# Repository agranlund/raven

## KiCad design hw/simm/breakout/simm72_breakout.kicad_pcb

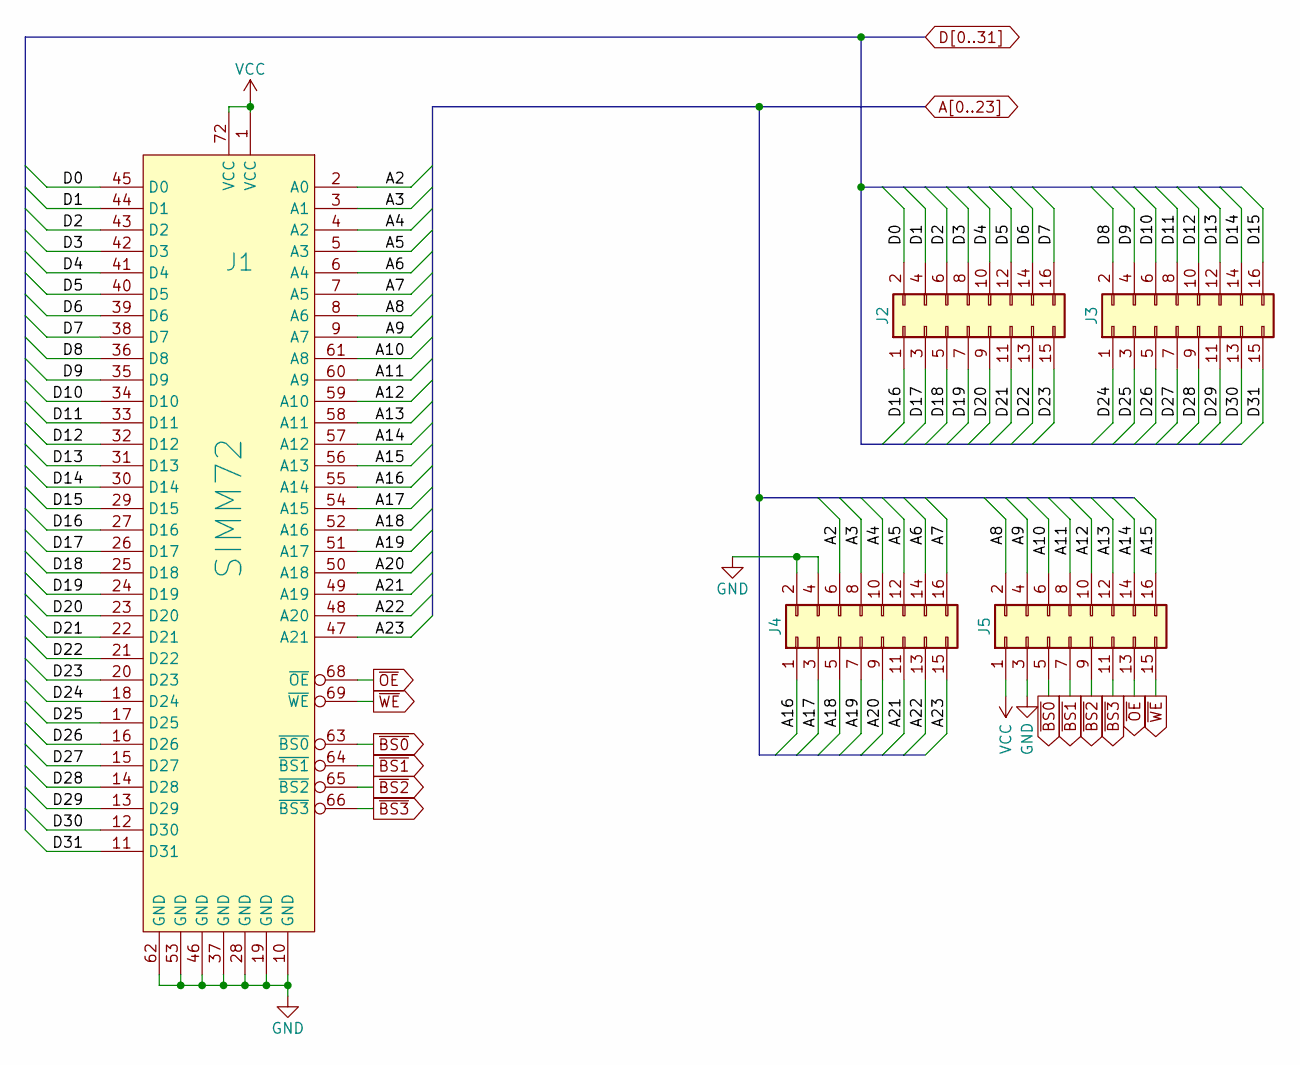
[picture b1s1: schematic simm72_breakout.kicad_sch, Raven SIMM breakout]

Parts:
J1: SIMM72; SIMM72_edge
J2, J3, J4, J5: Conn_02x08_Row_Letter_Last; PinHeader_2x08_P2.54mm_Vertical

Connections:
A2: J1.2 (A0), J4.6
A3: J1.3 (A1), J4.8
A4: J1.4 (A2), J4.10
A5: J1.5 (A3), J4.12
A6: J1.6 (A4), J4.14
A7: J1.7 (A5), J4.16
A8: J1.8 (A6), J5.2
A9: J1.9 (A7), J5.4
A10: J1.61 (A8), J5.6
A11: J1.60 (A9), J5.8
A12: J1.59 (A10), J5.10
A13: J1.58 (A11), J5.12
A14: J1.57 (A12), J5.14
A15: J1.56 (A13), J5.16
A16: J1.55 (A14), J4.1
A17: J1.54 (A15), J4.3
A18: J1.52 (A16), J4.5
A19: J1.51 (A17), J4.7
A20: J1.50 (A18), J4.9
A21: J1.49 (A19), J4.11
A22: J1.48 (A20), J4.13
A23: J1.47 (A21), J4.15
D0: J1.45 (D0), J2.2
D1: J1.44 (D1), J2.4
D2: J1.43 (D2), J2.6
D3: J1.42 (D3), J2.8
D4: J1.41 (D4), J2.10
D5: J1.40 (D5), J2.12
D6: J1.39 (D6), J2.14
D7: J1.38 (D7), J2.16
D8: J1.36 (D8), J3.2
D9: J1.35 (D9), J3.4
D10: J1.34 (D10), J3.6
D11: J1.33 (D11), J3.8
D12: J1.32 (D12), J3.10
D13: J1.31 (D13), J3.12
D14: J1.30 (D14), J3.14
D15: J1.29 (D15), J3.16
D16: J1.27 (D16), J2.1
D17: J1.26 (D17), J2.3
D18: J1.25 (D18), J2.5
D19: J1.24 (D19), J2.7
D20: J1.23 (D20), J2.9
D21: J1.22 (D21), J2.11
D22: J1.21 (D22), J2.13
D23: J1.20 (D23), J2.15
D24: J1.18 (D24), J3.1
D25: J1.17 (D25), J3.3
D26: J1.16 (D26), J3.5
D27: J1.15 (D27), J3.7
D28: J1.14 (D28), J3.9
D29: J1.13 (D29), J3.11
D30: J1.12 (D30), J3.13
D31: J1.11 (D31), J3.15
GND: J1.10 (GND), J1.19 (GND), J1.28 (GND), J1.37 (GND), J1.46 (GND), J1.53 (GND), J1.62 (GND), J4.2, J4.4, J5.3
VCC: J1.1 (VCC), J1.72 (VCC), J5.1
~BS0: J1.63 (~BS0), J5.5
~BS1: J1.64 (~BS1), J5.7
~BS2: J1.65 (~BS2), J5.9
~BS3: J1.66 (~BS3), J5.11
~OE: J1.68 (~OE), J5.13
~WE: J1.69 (~WE), J5.15

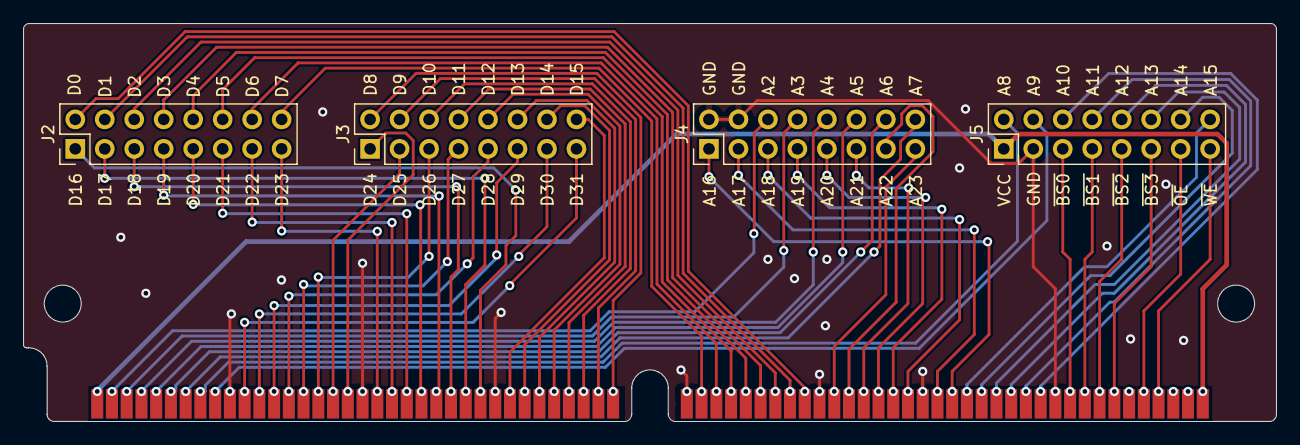
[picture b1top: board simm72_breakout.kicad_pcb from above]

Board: 2 copper layers, 108.0 x 34.3 mm, 5 parts (0 on the bottom side), 62 nets.

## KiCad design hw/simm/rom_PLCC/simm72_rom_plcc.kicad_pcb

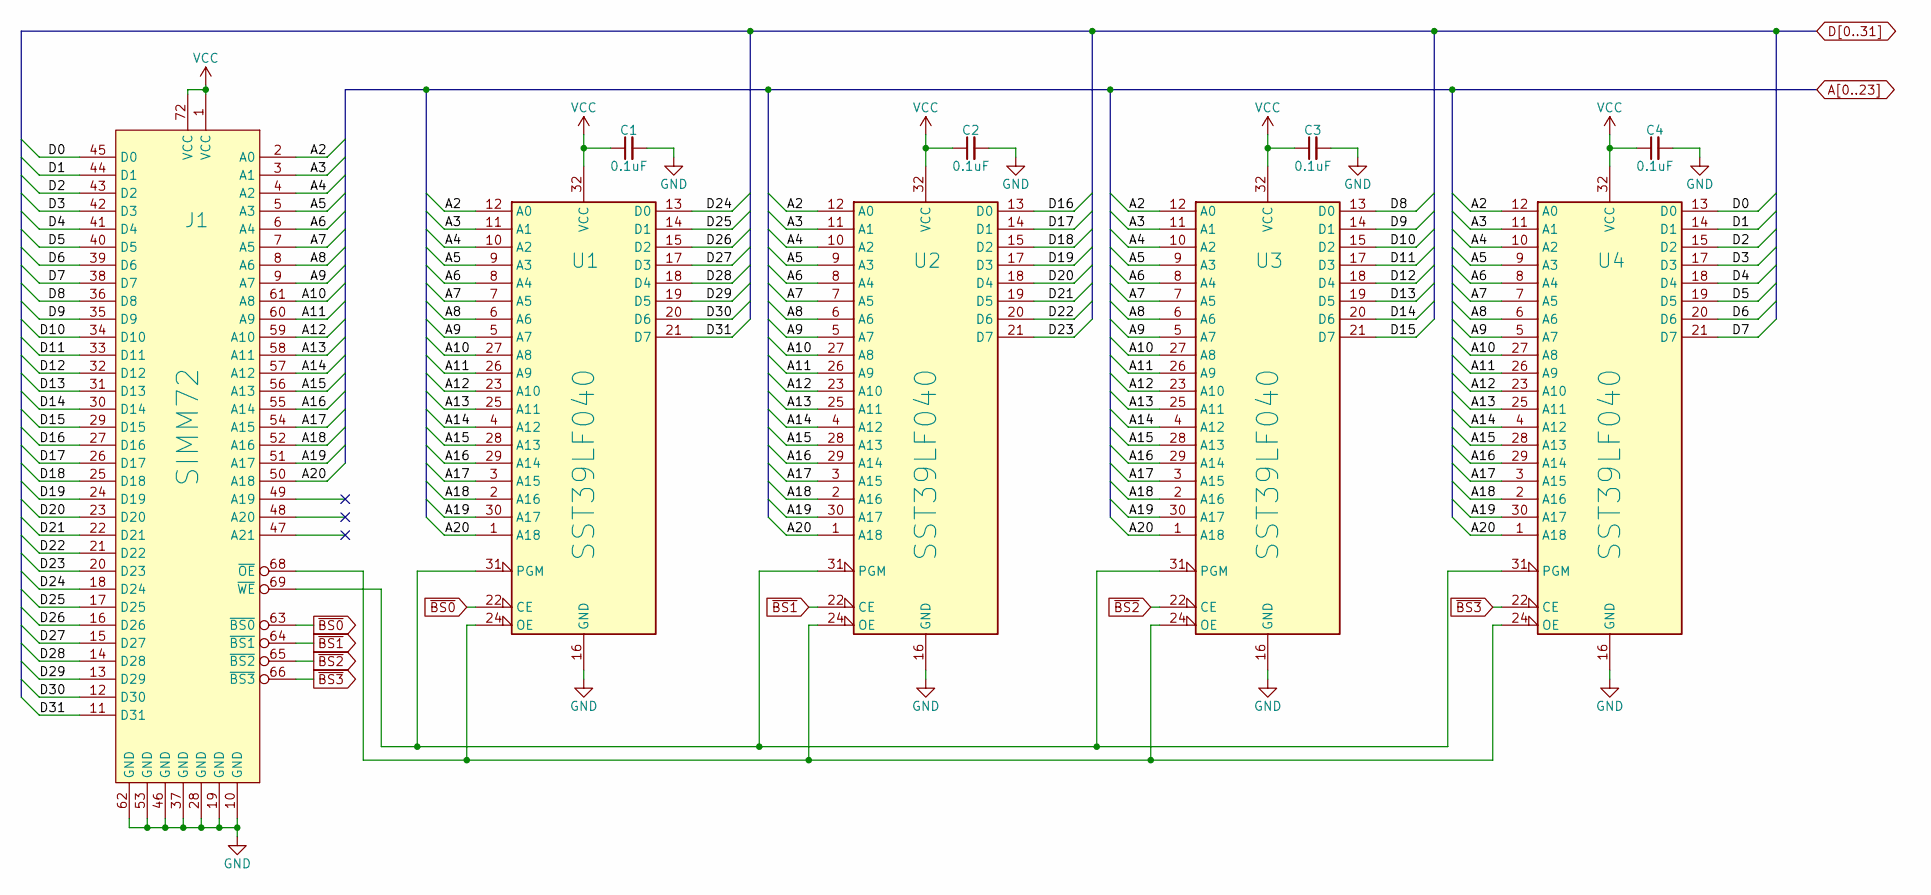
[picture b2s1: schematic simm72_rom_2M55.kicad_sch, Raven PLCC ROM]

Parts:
C1, C2, C3, C4: 0.1uF; C_1206_3216Metric_Pad1.33x1.80mm_HandSolder; Manufacturer_Part_Number C1206C104K5RACTU
J1: SIMM72; SIMM72_edge
U1, U2, U3, U4: SST39LF040; PLCC-32_THT-Socket; Manufacturer_Part_Number SST39LF040-55-4C-NHE-T

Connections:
A2: J1.2 (A0), U1.12 (A0), U2.12 (A0), U3.12 (A0), U4.12 (A0)
A3: J1.3 (A1), U1.11 (A1), U2.11 (A1), U3.11 (A1), U4.11 (A1)
A4: J1.4 (A2), U1.10 (A2), U2.10 (A2), U3.10 (A2), U4.10 (A2)
A5: J1.5 (A3), U1.9 (A3), U2.9 (A3), U3.9 (A3), U4.9 (A3)
A6: J1.6 (A4), U1.8 (A4), U2.8 (A4), U3.8 (A4), U4.8 (A4)
A7: J1.7 (A5), U1.7 (A5), U2.7 (A5), U3.7 (A5), U4.7 (A5)
A8: J1.8 (A6), U1.6 (A6), U2.6 (A6), U3.6 (A6), U4.6 (A6)
A9: J1.9 (A7), U1.5 (A7), U2.5 (A7), U3.5 (A7), U4.5 (A7)
A10: J1.61 (A8), U1.27 (A8), U2.27 (A8), U3.27 (A8), U4.27 (A8)
A11: J1.60 (A9), U1.26 (A9), U2.26 (A9), U3.26 (A9), U4.26 (A9)
A12: J1.59 (A10), U1.23 (A10), U2.23 (A10), U3.23 (A10), U4.23 (A10)
A13: J1.58 (A11), U1.25 (A11), U2.25 (A11), U3.25 (A11), U4.25 (A11)
A14: J1.57 (A12), U1.4 (A12), U2.4 (A12), U3.4 (A12), U4.4 (A12)
A15: J1.56 (A13), U1.28 (A13), U2.28 (A13), U3.28 (A13), U4.28 (A13)
A16: J1.55 (A14), U1.29 (A14), U2.29 (A14), U3.29 (A14), U4.29 (A14)
A17: J1.54 (A15), U1.3 (A15), U2.3 (A15), U3.3 (A15), U4.3 (A15)
A18: J1.52 (A16), U1.2 (A16), U2.2 (A16), U3.2 (A16), U4.2 (A16)
A19: J1.51 (A17), U1.30 (A17), U2.30 (A17), U3.30 (A17), U4.30 (A17)
A20: J1.50 (A18), U1.1 (A18), U2.1 (A18), U3.1 (A18), U4.1 (A18)
D0: J1.45 (D0), U4.13 (D0)
D1: J1.44 (D1), U4.14 (D1)
D2: J1.43 (D2), U4.15 (D2)
D3: J1.42 (D3), U4.17 (D3)
D4: J1.41 (D4), U4.18 (D4)
D5: J1.40 (D5), U4.19 (D5)
D6: J1.39 (D6), U4.20 (D6)
D7: J1.38 (D7), U4.21 (D7)
D8: J1.36 (D8), U3.13 (D0)
D9: J1.35 (D9), U3.14 (D1)
D10: J1.34 (D10), U3.15 (D2)
D11: J1.33 (D11), U3.17 (D3)
D12: J1.32 (D12), U3.18 (D4)
D13: J1.31 (D13), U3.19 (D5)
D14: J1.30 (D14), U3.20 (D6)
D15: J1.29 (D15), U3.21 (D7)
D16: J1.27 (D16), U2.13 (D0)
D17: J1.26 (D17), U2.14 (D1)
D18: J1.25 (D18), U2.15 (D2)
D19: J1.24 (D19), U2.17 (D3)
D20: J1.23 (D20), U2.18 (D4)
D21: J1.22 (D21), U2.19 (D5)
D22: J1.21 (D22), U2.20 (D6)
D23: J1.20 (D23), U2.21 (D7)
D24: J1.18 (D24), U1.13 (D0)
D25: J1.17 (D25), U1.14 (D1)
D26: J1.16 (D26), U1.15 (D2)
D27: J1.15 (D27), U1.17 (D3)
D28: J1.14 (D28), U1.18 (D4)
D29: J1.13 (D29), U1.19 (D5)
D30: J1.12 (D30), U1.20 (D6)
D31: J1.11 (D31), U1.21 (D7)
GND: C1.2, C2.2, C3.2, C4.2, J1.10 (GND), J1.19 (GND), J1.28 (GND), J1.37 (GND), J1.46 (GND), J1.53 (GND), J1.62 (GND), U1.16 (GND), U2.16 (GND), U3.16 (GND), U4.16 (GND)
unnamed: J1.68 (~OE), U1.24 (OE), U2.24 (OE), U3.24 (OE), U4.24 (OE)
unnamed: J1.69 (~WE), U1.31 (PGM), U2.31 (PGM), U3.31 (PGM), U4.31 (PGM)
VCC: C1.1, C2.1, C3.1, C4.1, J1.1 (VCC), J1.72 (VCC), U1.32 (VCC), U2.32 (VCC), U3.32 (VCC), U4.32 (VCC)
~BS0: J1.63 (~BS0), U1.22 (CE)
~BS1: J1.64 (~BS1), U2.22 (CE)
~BS2: J1.65 (~BS2), U3.22 (CE)
~BS3: J1.66 (~BS3), U4.22 (CE)

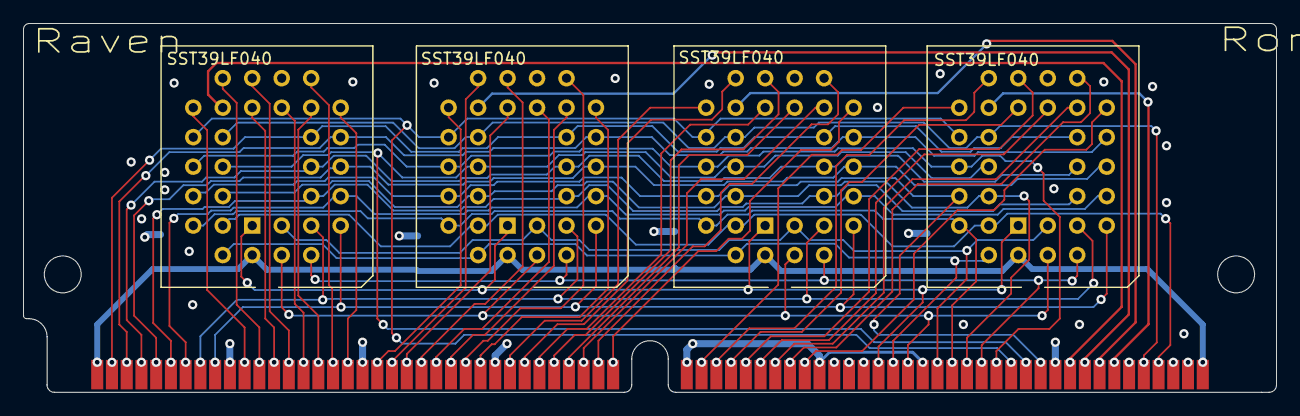
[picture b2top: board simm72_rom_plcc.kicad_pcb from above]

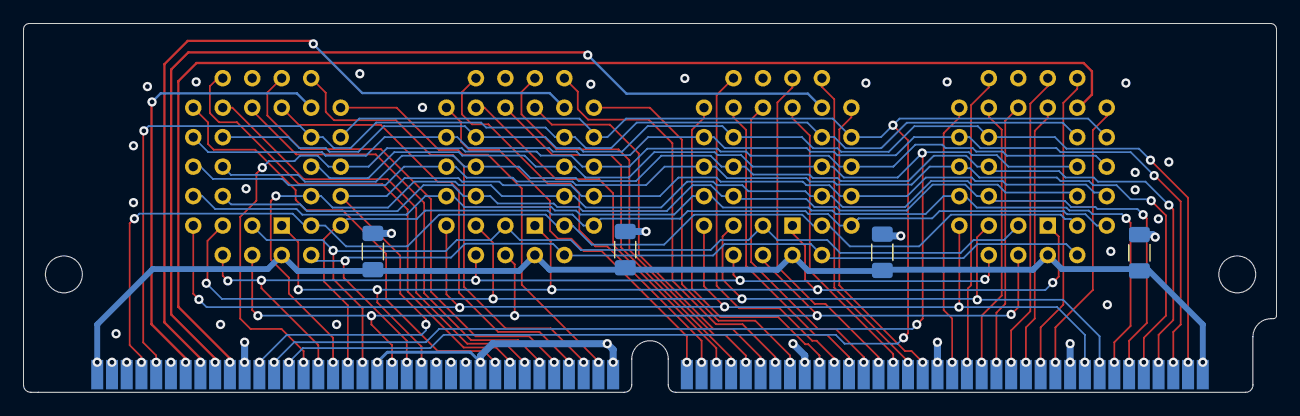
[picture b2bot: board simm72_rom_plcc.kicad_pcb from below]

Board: 4 copper layers, 108.0 x 31.8 mm, 9 parts (4 on the bottom side), 59 nets.

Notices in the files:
hw/simm/breakout/simm72_breakout.kicad_pcb:
Licensed under CERN-OHL-P v2
